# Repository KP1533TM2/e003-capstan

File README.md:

# e003-capstan
Проект блока управления ведущими двигателями ДМ-1, ДМ-5 (применяемые в магнитофонах Олимп, Электроника ТА1-003) с кварцевой стабилизацией.

Основан на коде [контроллера ведущего двигателя самодельной кассетной деки TK-140 leoniv](http://leoniv.diod.club/projects/audio/tk-140/tk-140.html).

ZCD для сетевого напряжения взят и адаптирован [отсюда](https://cdn.hackaday.io/files/1597066832861504/SimpleIsolatedZeroCrossDetector.pdf).

# Отличия от БУВД Олимп 005
- Иной форм-фактор платы (расчитано на доработанный Олимп 003);
- Силовой каскад реализован простым преобразователем напряжения в ток;
- ФАПЧ, формирование синусоидального тока выполнены на микроконтроллере;
- Реализовано торможение при смене скорости кратковременным реверсом;

# Схема
Актуальная версия схемы (для rev1) лежит [тут](/hw/rev1/main.pdf).

# TODO:
- [x] "чистовая" плата - предположительно rev1;
- [ ] АПЧ сетевого напряжения;
- [ ] переключение реле синхронно переходу через 0 для сбережения контактов (?);
- [ ] описание.

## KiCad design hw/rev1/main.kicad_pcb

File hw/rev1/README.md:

# Краткое описание rev1

Ревизия 1 - первая "чистовая" печатная плата.

[Схема этой платы](./main.pdf).

Основные моменты:
* Сложная оригинальная схема петлевого фильтра, модулятора тока и силового
каскада полностью заменена на фильтр ШИМ с преобразователем V→I с применением
полевого транзистора.
* Модуляция синусом реализована таблично и воздействует на выход PID-регулятора.
* Интервал полупериода сетевого напряжения снимается посредством схемы ZCD с
обмотки трансформатора, питающей ведущий двигатель.
* Номиналы схемы ZCD эмпирически подобраны так, чтобы при трехступенчатой форме
сетевого напряжения (с ИБП) схема стабильно формировала лог.0 при "ступеньке"
0В;
* Добавлены крепежные отверстия по периметру.

# Картинки

To be continued...

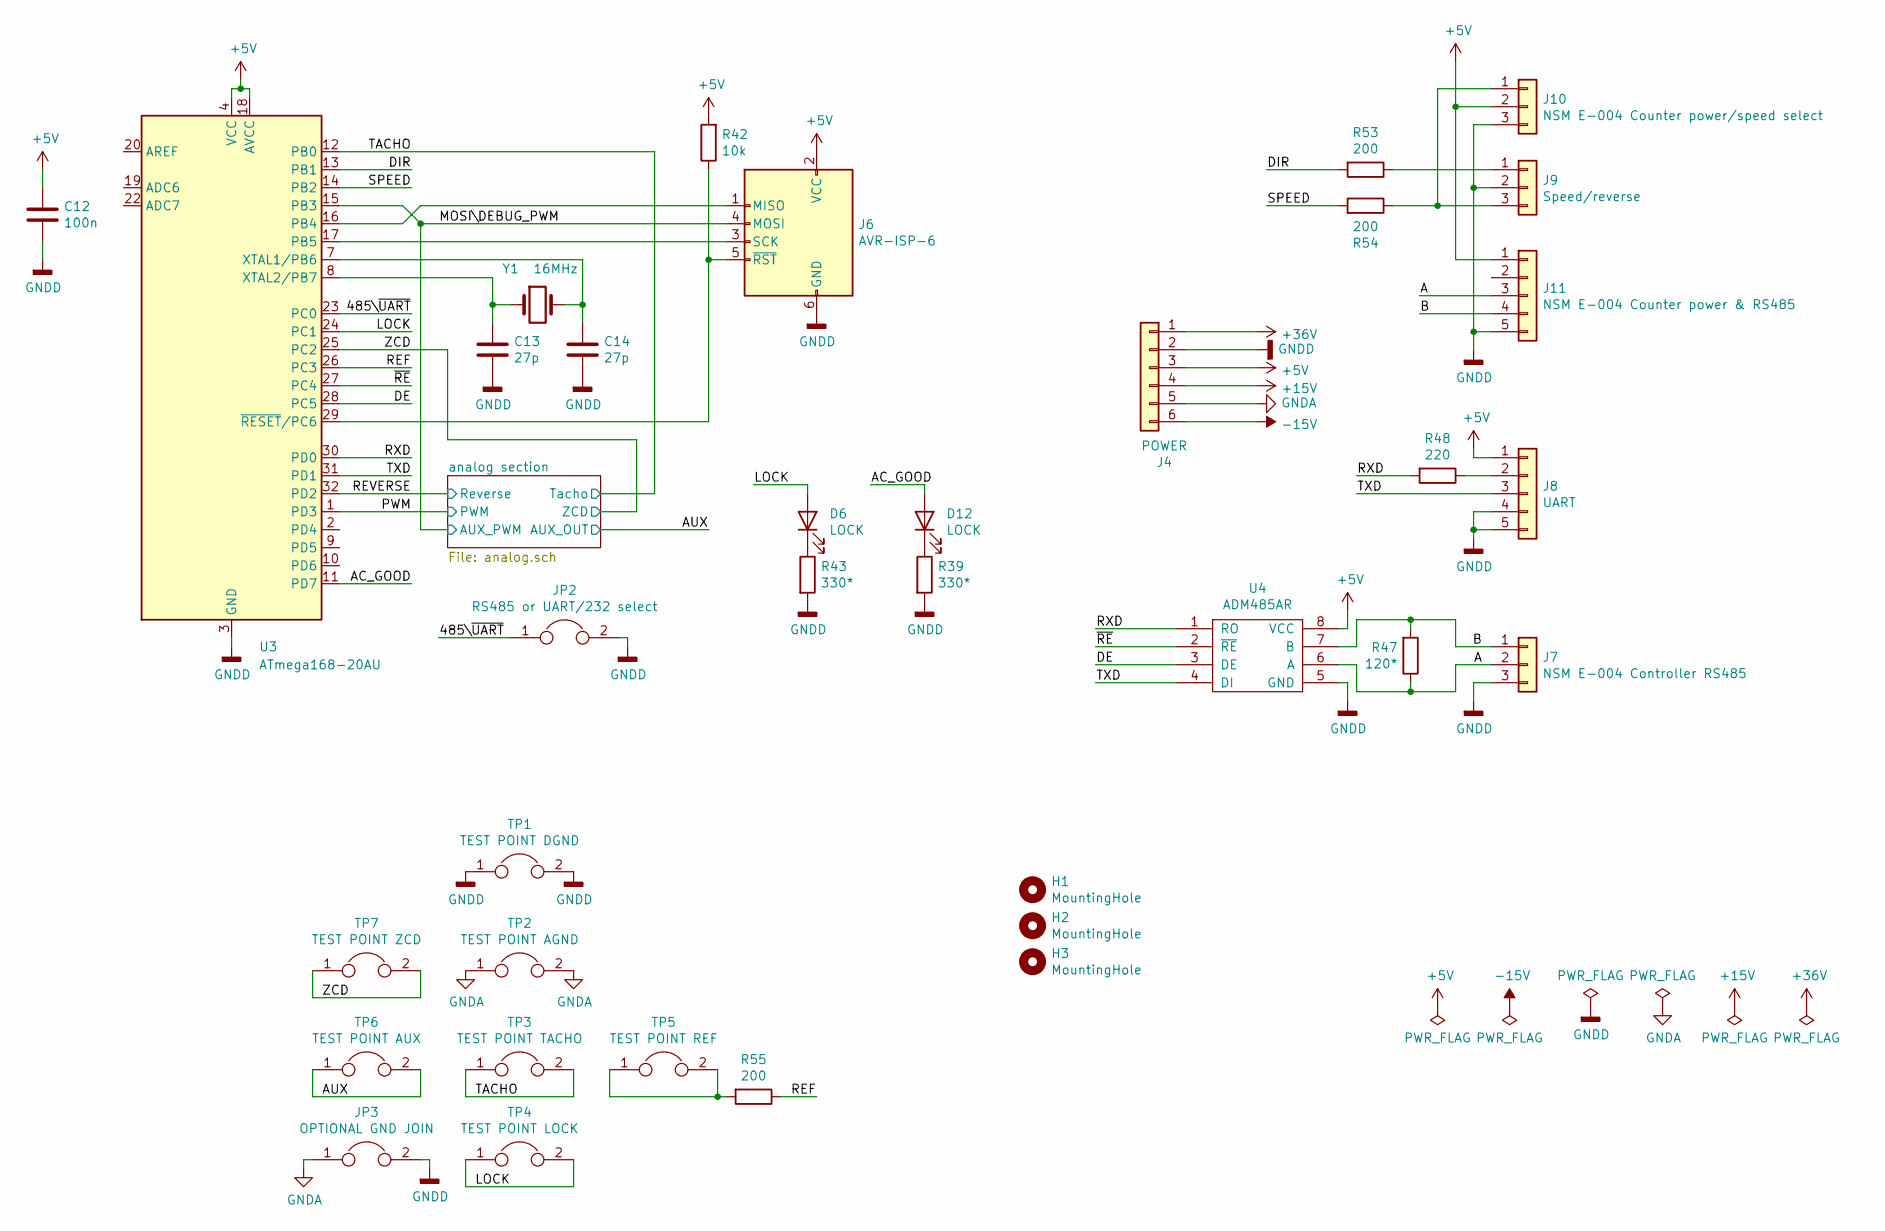
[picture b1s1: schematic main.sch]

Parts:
C12: 100n; C_0805_2012Metric
C13, C14: 27p; C_0805_2012Metric
D6, D12: LOCK; LED_0805_2012Metric
H1, H2, H3: MountingHole; MountingHole_3.2mm_M3
J4: POWER; Molex_KK-396_Right_Angle
J6: AVR-ISP-6; PinHeader_2x03_P2.54mm_Vertical
J7: NSM E-004 Controller RS485; JST_XH_B3B-XH-A_1x03_P2.50mm_Vertical
J8: UART; JST_XH_B5B-XH-A_1x05_P2.50mm_Vertical
J9: Speed/reverse; JST_XH_B3B-XH-A_1x03_P2.50mm_Vertical
J10: NSM E-004 Counter power/speed select; JST_XH_B3B-XH-A_1x03_P2.50mm_Vertical
J11: NSM E-004 Counter power & RS485; JST_XH_B5B-XH-A_1x05_P2.50mm_Vertical
JP2: RS485 or UART/232 select; PinHeader_1x02_P2.54mm_Vertical
JP3: OPTIONAL GND JOIN; SolderJumper-2_P1.3mm_Open_RoundedPad1.0x1.5mm
R39, R43: 330*; R_0805_2012Metric
R42: 10k; R_0805_2012Metric
R47: 120*; R_0805_2012Metric
R48: 220; R_0805_2012Metric
R53, R54, R55: 200; R_0805_2012Metric
TP1: TEST POINT DGND; PinHeader_2x01_P2.54mm_Vertical
TP2: TEST POINT AGND; PinHeader_2x01_P2.54mm_Vertical
TP3: TEST POINT TACHO; PinHeader_2x01_P2.54mm_Vertical
TP4: TEST POINT LOCK; PinHeader_2x01_P2.54mm_Vertical
TP5: TEST POINT REF; PinHeader_2x01_P2.54mm_Vertical
TP6: TEST POINT AUX; PinHeader_2x01_P2.54mm_Vertical
TP7: TEST POINT ZCD; PinHeader_2x01_P2.54mm_Vertical
U3: ATmega168-20AU; TQFP-32_7x7mm_P0.8mm
U4: ADM485AR; SO-8_3.9x4.9mm_P1.27mm
Y1: 16MHz; Crystal_SMD_HC49-SD

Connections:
+5V: C12.1, J4.3, J6.2 (VCC), J8.1, J10.2, J11.1, R42.2, U3.4 (VCC), U3.6 (VCC), U3.18 (AVCC), U4.8 (VCC); also elsewhere on the board
+15V: J4.4; also elsewhere on the board
+36V: J4.1; also elsewhere on the board
-15V: J4.6; also elsewhere on the board
/485\~UART: JP2.1, U3.23 (PC0)
/A: J7.2, J11.3, R47.1, U4.6 (A)
/AC_GOOD: D12.2 (A), U3.11 (PD7)
/AUX: TP6.1, TP6.2; also elsewhere on the board
/B: J7.1, J11.4, R47.2, U4.7 (B)
/DE: U3.28 (PC5), U4.3 (DE)
/DIR: R53.2, U3.13 (PB1)
/LOCK: D6.2 (A), TP4.1, TP4.2, U3.24 (PC1)
/MOSI\DEBUG_PWM: J6.4 (MOSI), U3.15 (PB3); also elsewhere on the board
/PWM: U3.1 (PD3); also elsewhere on the board
/REF: R55.1, U3.26 (PC3)
/REVERSE: U3.32 (PD2); also elsewhere on the board
/RXD: R48.2, U3.30 (PD0), U4.1 (RO)
/SPEED: R54.2, U3.14 (PB2)
/TACHO: TP3.1, TP3.2, U3.12 (PB0); also elsewhere on the board
/TXD: J8.3, U3.31 (PD1), U4.4 (DI)
/ZCD: TP7.1, TP7.2, U3.25 (PC2); also elsewhere on the board
/~RE: U3.27 (PC4), U4.2 (~RE)
GNDA: J4.5, JP3.1, TP2.1, TP2.2; also elsewhere on the board
GNDD: C12.2, C13.2, C14.2, J4.2, J6.6 (GND), J7.3, J8.4, J8.5, J9.2, J10.3, J11.5, JP2.2, JP3.2, R39.2, R43.2, TP1.1, TP1.2, U3.3 (GND), U3.5 (GND), U3.21 (GND), U4.5 (GND); also elsewhere on the board
unnamed: C13.1, U3.8 (XTAL2/PB7), Y1.1
unnamed: C14.1, U3.7 (XTAL1/PB6), Y1.2
unnamed: D6.1 (K), R43.1
unnamed: D12.1 (K), R39.1
unnamed: J6.1 (MISO), U3.16 (PB4)
unnamed: J6.3 (SCK), U3.17 (PB5)
unnamed: J6.5 (~RST), R42.1, U3.29 (~RESET~/PC6)
unnamed: J8.2, R48.1
unnamed: J9.1, R53.1
unnamed: J9.3, J10.1, R54.1
unnamed: R55.2, TP5.1, TP5.2

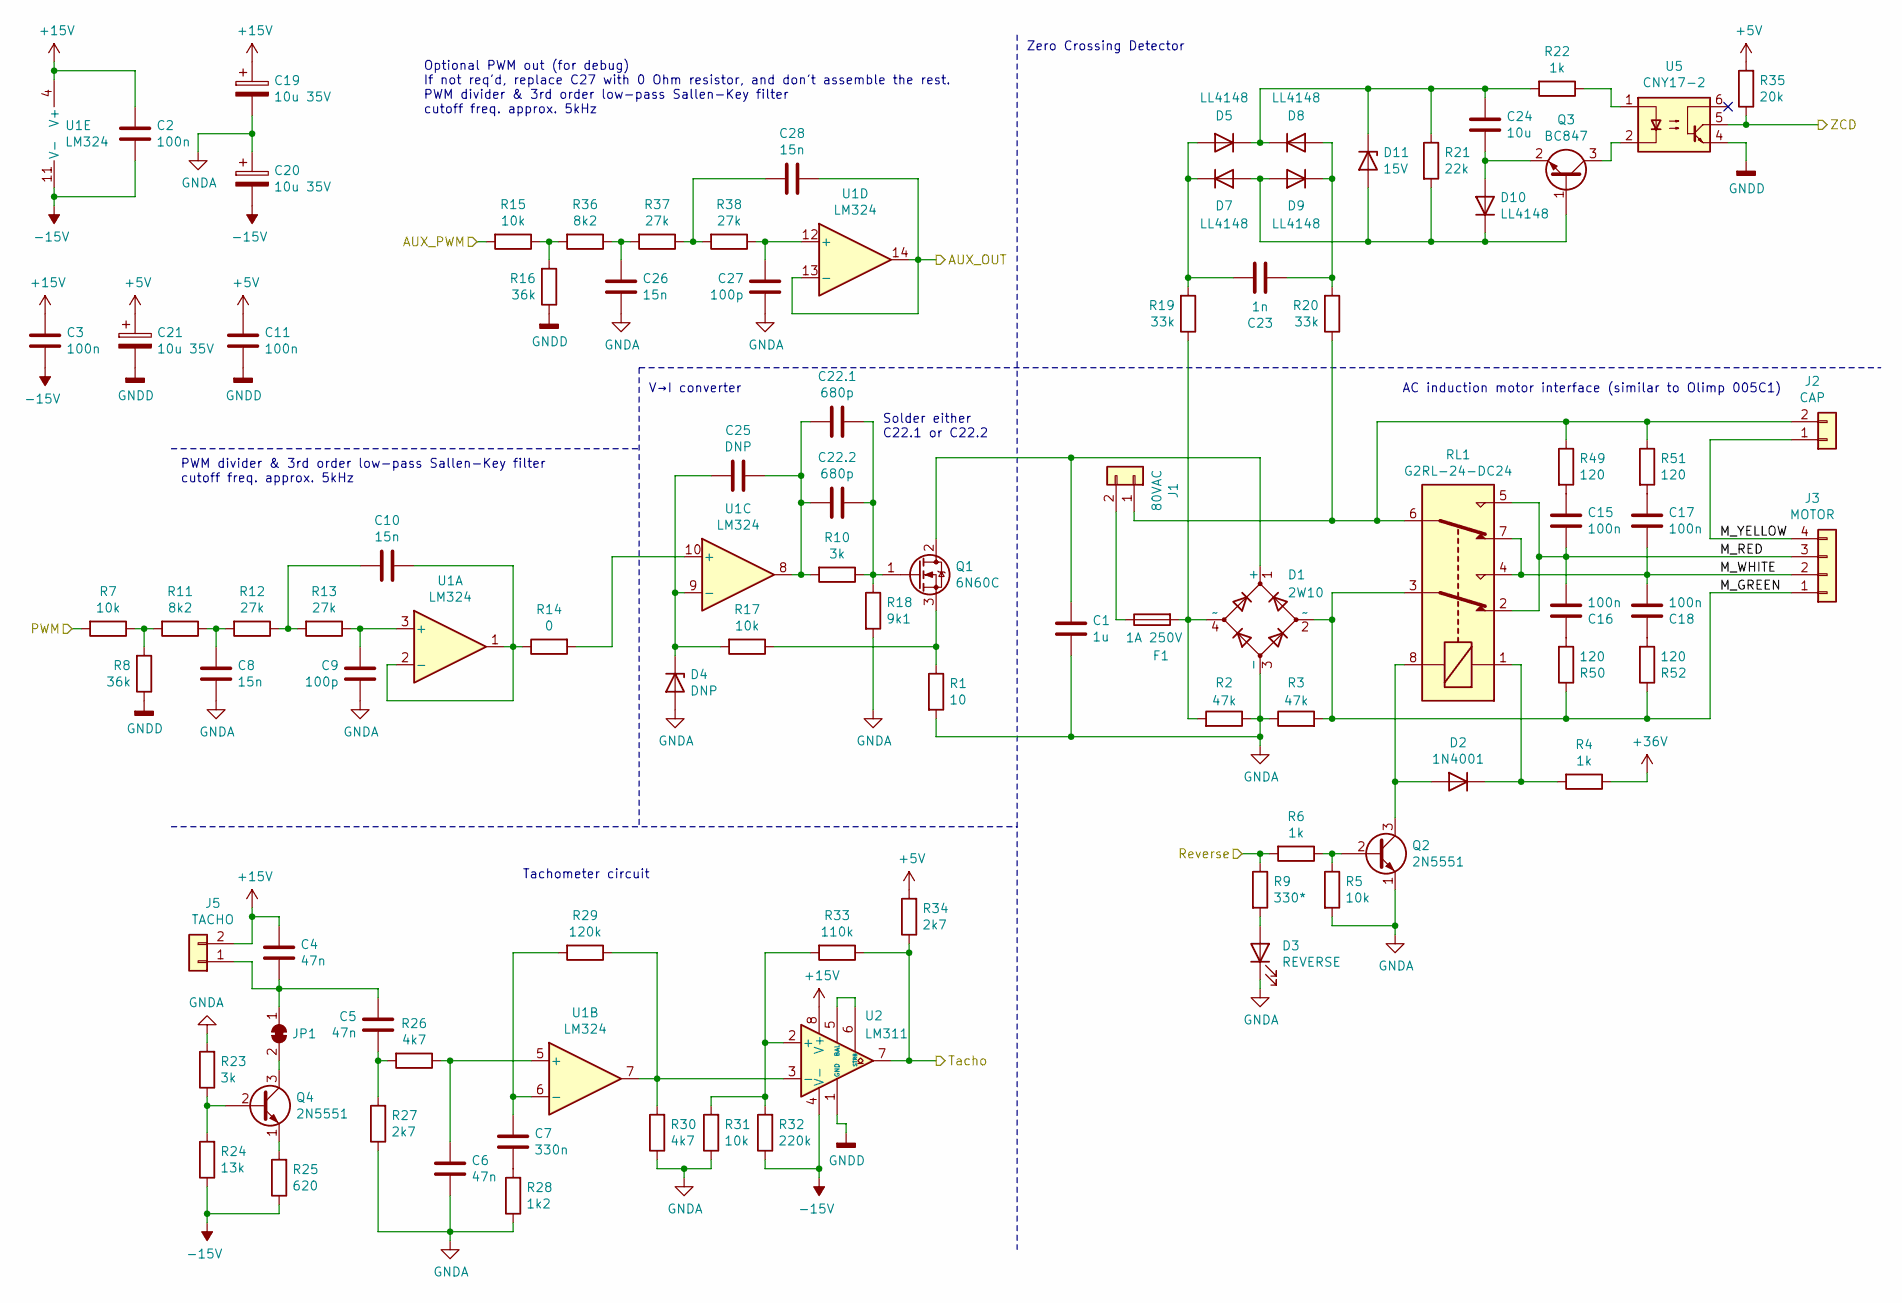
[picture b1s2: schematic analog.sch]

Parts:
C1: 1u; C_Rect_L29.0mm_W12.2mm_P27.50mm_MKT
C2, C3, C11: 100n; C_0805_2012Metric
C4, C5, C6: 47n; C_0805_2012Metric
C7: 330n; C_0805_2012Metric
C8, C10, C26, C28: 15n; C_0805_2012Metric
C9, C27: 100p; C_0805_2012Metric
C15, C16, C17, C18: 100n; C_Rect_L13.0mm_W4.0mm_P10.00mm_FKS3_FKP3_MKS4
C19, C20, C21: 10u 35V; CP_EIA-6032-28_Kemet-C
C22.1: 680p; C_Rect_L7.0mm_W4.5mm_P5.00mm
C22.2: 680p; C_0805_2012Metric
C23: 1n; C_1206_3216Metric
C24: 10u; C_1206_3216Metric
C25: DNP; C_0805_2012Metric
D1: 2W10; Diode_Bridge_Round_D9.8mm
D2: 1N4001; D_DO-41_SOD81_P5.08mm_Vertical_KathodeUp
D3: REVERSE; LED_0805_2012Metric
D4: DNP; D_SOD-123
D5, D7, D8, D9, D10: LL4148; D_MiniMELF
D11: 15V; D_SOD-123
F1: 1A 250V; Fuse_Littelfuse_372_D8.50mm
J1: 80VAC; TerminalBlock_bornier-2_P5.08mm
J2: CAP; TerminalBlock_bornier-2_P5.08mm
J3: MOTOR; TerminalBlock_bornier-4_P5.08mm
J5: TACHO; Molex_KK-254_AE-6410-02A_1x02_P2.54mm_Vertical
JP1: SolderJumper_2_Bridged; SolderJumper-2_P1.3mm_Bridged_RoundedPad1.0x1.5mm
Q1: 6N60C; TO-220F-3_Horizontal_TabDown_no_silk
Q2, Q4: 2N5551; TO-92L_Inline_Wide
Q3: BC847; SOT-23
R1: 10; R_Axial_DIN0922_L20.0mm_D9.0mm_P30.48mm_Horizontal
R2, R3: 47k; R_Axial_DIN0207_L6.3mm_D2.5mm_P5.08mm_Vertical
R4: 1k; R_Axial_DIN0614_L14.3mm_D5.7mm_P5.08mm_Vertical
R5, R7, R15, R31: 10k; R_0805_2012Metric
R6: 1k; R_0805_2012Metric
R8, R16: 36k; R_0805_2012Metric
R9: 330*; R_0805_2012Metric
R10: 3k; R_Axial_DIN0207_L6.3mm_D2.5mm_P10.16mm_Horizontal
R11, R36: 8k2; R_0805_2012Metric
R12, R13, R37, R38: 27k; R_0805_2012Metric
R14: 0; R_0805_2012Metric
R17: 10k; R_Axial_DIN0207_L6.3mm_D2.5mm_P10.16mm_Horizontal
R18: 9k1; R_Axial_DIN0207_L6.3mm_D2.5mm_P10.16mm_Horizontal
R19, R20: 33k; R_1206_3216Metric
R21: 22k; R_1206_3216Metric
R22: 1k; R_1206_3216Metric
R23: 3k; R_0805_2012Metric
R24: 13k; R_0805_2012Metric
R25: 620; R_0805_2012Metric
R26, R30: 4k7; R_0805_2012Metric
R27, R34: 2k7; R_0805_2012Metric
R28: 1k2; R_0805_2012Metric
R29: 120k; R_0805_2012Metric
R32: 220k; R_0805_2012Metric
R33: 110k; R_0805_2012Metric
R35: 20k; R_0805_2012Metric
R49, R50, R51, R52: 120; R_Axial_DIN0309_L9.0mm_D3.2mm_P5.08mm_Vertical
RL1: G2RL-24-DC24; Relay_DPDT_Omron_G2RL
U1: LM324; SO-14_3.9x8.65mm_P1.27mm
U2: LM311; SO-8_3.9x4.9mm_P1.27mm
U5: CNY17-2; DIP-6_W7.62mm_LongPads

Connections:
+5V: C11.1, C21.1, R34.2, R35.2; also elsewhere on the board
+15V: C2.1, C3.1, C4.1, C19.1, J5.2, U1.4 (V+), U2.8 (V+); also elsewhere on the board
+36V: R4.1; also elsewhere on the board
-15V: C2.2, C3.2, C20.2, R24.1, R25.1, R32.1, U1.11 (V-), U2.4 (V-); also elsewhere on the board
/AUX: C28.1, U1.13 (-), U1.14; also elsewhere on the board
/MOSI\DEBUG_PWM: R15.2; also elsewhere on the board
/PWM: R7.2; also elsewhere on the board
/REVERSE: R6.2, R9.1; also elsewhere on the board
/TACHO: R33.1, R34.1, U2.7; also elsewhere on the board
/ZCD: R35.1, U5.5; also elsewhere on the board
/analog section/M_GREEN: D1.2 (~~), J3.1, R3.2, R50.1, R52.1, RL1.3
/analog section/M_RED: C15.2, C16.2, J3.3, RL1.2, RL1.5
/analog section/M_WHITE: C17.2, C18.2, J3.2, RL1.4, RL1.7
/analog section/M_YELLOW: J2.1, J3.4
GNDA: C1.2, C6.2, C8.2, C9.2, C19.2, C20.1, C26.2, C27.2, D1.3 (-), D3.1 (K), D4.2 (A), Q2.1 (E), R1.2, R2.1, R3.1, R5.2, R18.2, R23.2, R27.1, R28.1, R30.1, R31.1; also elsewhere on the board
GNDD: C11.2, C21.2, R8.1, R16.1, U2.1 (GND), U5.4; also elsewhere on the board
unnamed: C1.1, D1.1 (+), Q1.2 (D)
unnamed: C4.2, C5.1, J5.1, JP1.1 (A)
unnamed: C5.2, R26.2, R27.2
unnamed: C6.1, R26.1, U1.5 (+)
unnamed: C7.1, R29.2, U1.6 (-)
unnamed: C7.2, R28.2
unnamed: C8.1, R11.1, R12.2
unnamed: C9.1, R13.1, U1.3 (+)
unnamed: C10.1, R14.1, U1.1, U1.2 (-)
unnamed: C10.2, R12.1, R13.2
unnamed: C15.1, R49.2
unnamed: C16.1, R50.2
unnamed: C17.1, R51.2
unnamed: C18.1, R52.2
unnamed: C22.1.1, C22.2.1, Q1.1 (G), R10.1, R18.1
unnamed: C22.1.2, C22.2.2, C25.1, R10.2, U1.8
unnamed: C23.1, D5.2 (A), D7.1 (K), R19.2
unnamed: C23.2, D8.2 (A), D9.1 (K), R20.2
unnamed: C24.1, D5.1 (K), D8.1 (K), D11.1 (K), R21.1, R22.2
unnamed: C24.2, D10.2 (A), Q3.2 (E)
unnamed: C25.2, D4.1 (K), R17.2, U1.9 (-)
unnamed: C26.1, R36.1, R37.2
unnamed: C27.1, R38.1, U1.12 (+)
unnamed: C28.2, R37.1, R38.2
unnamed: D1.4 (~~), F1.2, R2.2, R19.1
unnamed: D2.1 (K), R4.2, RL1.1
unnamed: D2.2 (A), Q2.3 (C), RL1.8
unnamed: D3.2 (A), R9.2
unnamed: D7.2 (A), D9.2 (A), D10.1 (K), D11.2 (A), Q3.1 (B), R21.2
unnamed: F1.1, J1.2
unnamed: J1.1, J2.2, R20.1, R49.1, R51.1, RL1.6
unnamed: JP1.2 (B), Q4.3 (C)
unnamed: Q1.3 (S), R1.1, R17.1
unnamed: Q2.2 (B), R5.1, R6.1
unnamed: Q3.3 (C), U5.2
unnamed: Q4.1 (E), R25.2
unnamed: Q4.2 (B), R23.1, R24.2
unnamed: R7.1, R8.2, R11.2
unnamed: R14.2, U1.10 (+)
unnamed: R15.1, R16.2, R36.2
unnamed: R22.1, U5.1
unnamed: R29.1, R30.2, U1.7, U2.3 (-)
unnamed: R31.2, R32.2, R33.2, U2.2 (+)
unnamed: U2.5 (BAL), U2.6 (STRB)

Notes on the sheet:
PWM divider & 3rd order low-pass Sallen-Key filter cutoff freq. approx. 5kHz
V→I converter
Tachometer circuit
AC induction motor interface (similar to Olimp 005C1)
Zero Crossing Detector
Optional PWM out (for debug) If not req'd, replace C27 with 0 Ohm resistor, and don't assemble the rest. PWM divider & 3rd order low-pass Sallen-Key filter cutoff freq. approx. 5kHz
Solder either C22.1 or C22.2

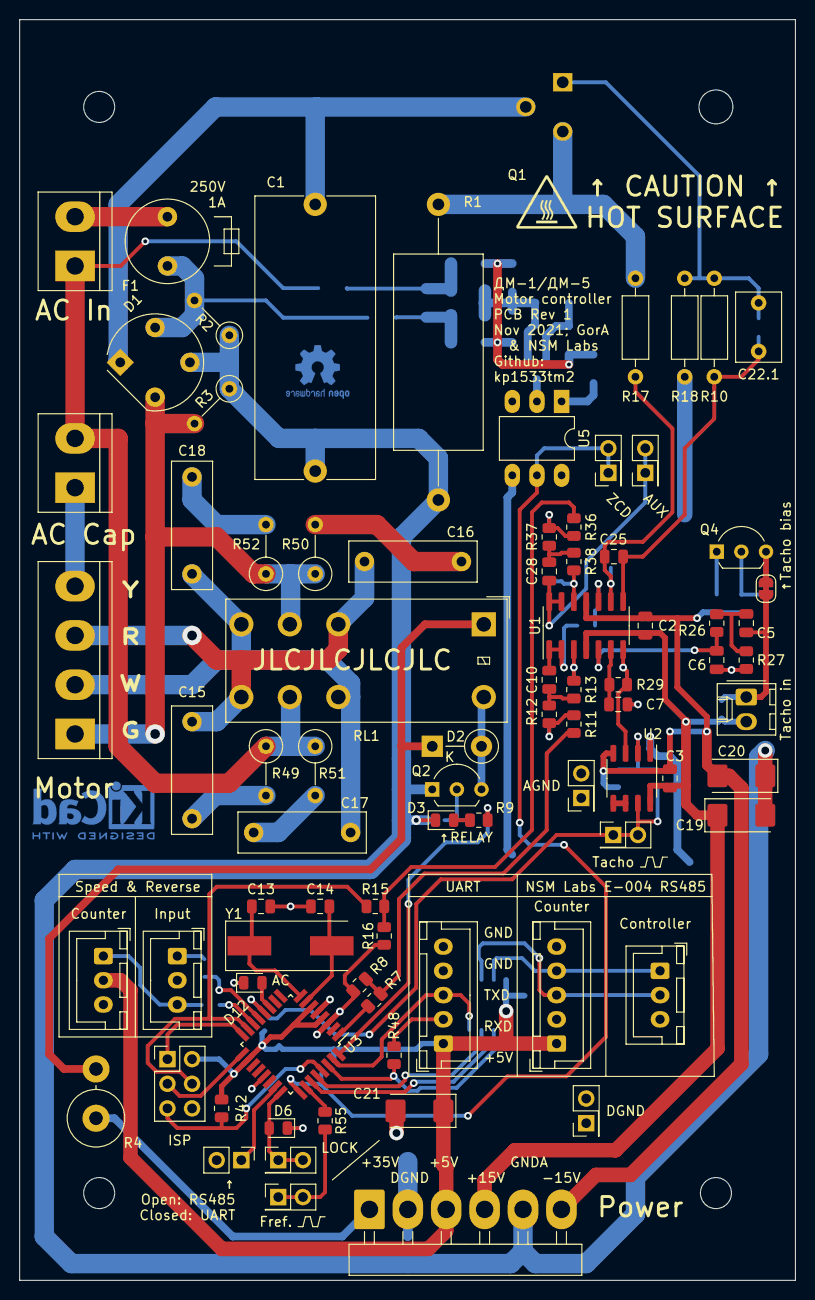
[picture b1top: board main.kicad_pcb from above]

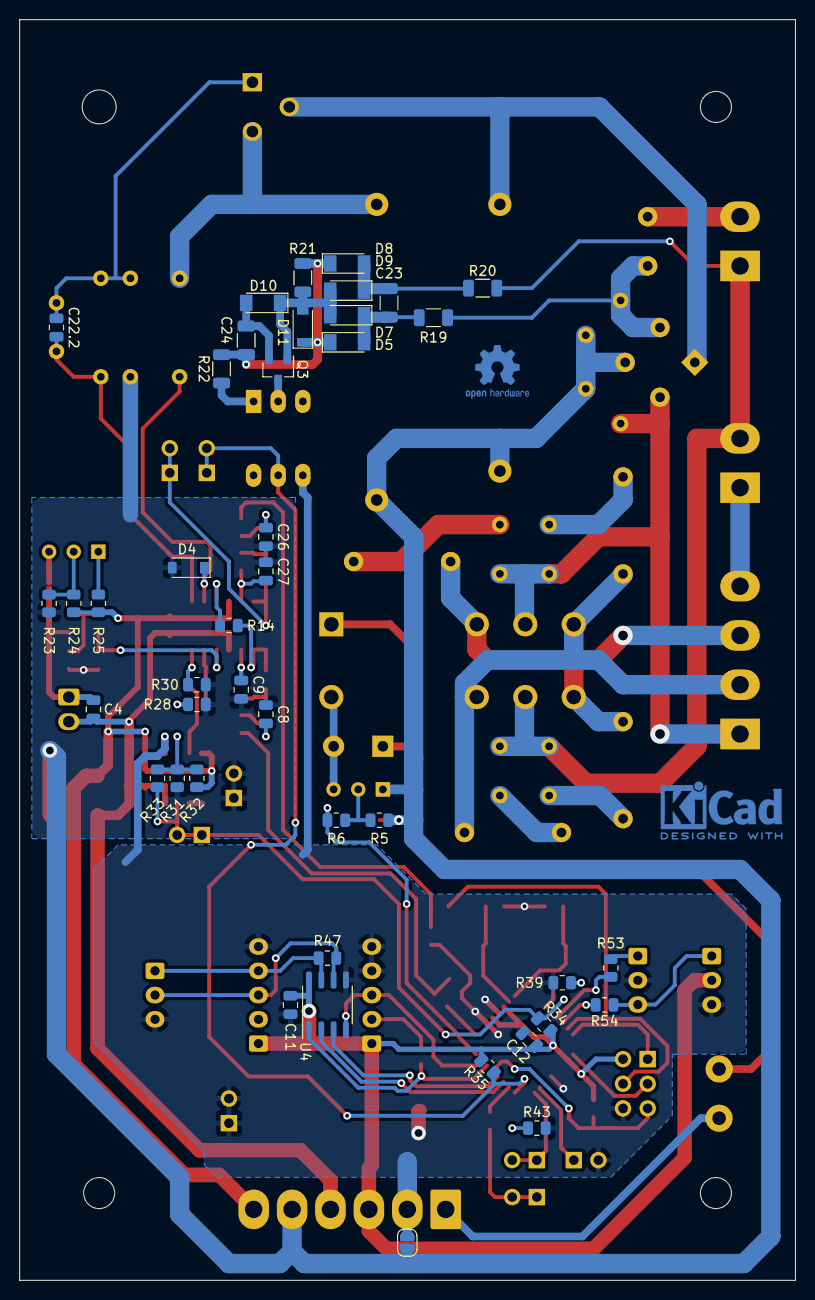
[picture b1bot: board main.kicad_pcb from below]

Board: 2 copper layers, 80.0 x 130.0 mm, 127 parts (42 on the bottom side), 83 nets.

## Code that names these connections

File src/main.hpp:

//----------------------------------------------------------------------------

//Главный модуль, заголовочный файл

//----------------------------------------------------------------------------

#ifndef MAIN_HPP
#define MAIN_HPP

//----------------------------------------------------------------------------

#include <ioavr.h>
#include <intrinsics.h>
#define __STDC_LIMIT_MACROS
#include <stdint.h>
#include <stdbool.h>
#include "gpio.hpp"
#include "systimer.hpp"

//-------------------------- Номер версии firmware: --------------------------

#define VERSION "1.00"

//-------------- Использование выводов процессора [module]: ------------------

typedef TGpio<PORT_C, PIN_1> Pin_Led_t;   //PC1 - LED out [control]
typedef TGpio<PORT_D, PIN_2> Pin_Relay_t; //PD2 - Reverse relay
typedef TGpio<PORT_C, PIN_3> Pin_Fref_t;  //PC3 - Fref out (oscilloscope) (normally PC3)
typedef TGpio<PORT_C, PIN_4> Pin_Debug_t; //PC4 - Oscilloscope debug out
typedef TGpio<PORT_B, PIN_1> Pin_Dir_t;   //PB1 - Reverse [control]
typedef TGpio<PORT_B, PIN_2> Pin_Spd1_t;  //PB2 - Speed 1 [control], 9/19

typedef TGpio<PORT_B, PIN_0> Pin_Tacho_t; //PB0 (ICP0) - Tacho in [control]
typedef TGpio<PORT_D, PIN_3> Pin_Pwm_t;   //PB3 (OC2B) - PWM out [pwm]
typedef TGpio<PORT_C, PIN_2> Pin_Zcd_t;   //PC2 - Zero Crossing Detector

typedef TGpio<PORT_D, PIN_0> Pin_RXD_t;   //PD0 (RXD) - RXD [wakeport]
typedef TGpio<PORT_D, PIN_1> Pin_TXD_t;   //PD1 (TXD) - TXD [wakeport]

typedef TGpio<PORT_D, PIN_4> Pin_Lock_t;  //PD4 - Lock out [control] NOT USED
typedef TGpio<PORT_D, PIN_5> Pin_Sleep_t; //PD5 - Sleep [control] NOT USED
//typedef TGpio<PORT_D, PIN_6> Pin_Spd2_t;  //PD6 - Speed 2 [control], FWD/REV

//-------------- Использование аппаратных блоков процессора: -----------------

//Timer0: system timer [systimer]
//Timer1: reference divider [pll]
//Timer2: PWM generation [pwm]
//USART: computer port [wakeport]
//Comparator : NOT USED
//ADC: NOT USED
//SPI: NOT USED
//TWI: NOT USED

//----------------------- Использование прерываний: --------------------------

//TIMER0_COMPA: system tick [systimer]
//TIMER1_CAPT: speed sensor [pll]
//TIMER1_COMPA: phase estimation [pll]
//TIMER2_COMPA: delta-sigma modulator [pwm]

//---------------------------- Макроопределения: -----------------------------

#define LO(x)    ((uint8_t)((x) & 0xFF))
#define HI(x)    ((uint8_t)(((x) >> 8) & 0xFF))
#define BYTE1(x) (LO(x))
#define BYTE2(x) (HI(x))
#define BYTE3(x) ((uint8_t)(((uint32_t)(x) >> 16) & 0xFF))
#define BYTE4(x) ((uint8_t)(((uint32_t)(x) >> 24) & 0xFF))

#define WORD(b1,b0)        (((uint16_t)(b1) << 8) | (b0))
#define DWORD(b3,b2,b1,b0) (((uint32_t)WORD(b3,b2) << 16) | WORD(b1,b0))

#define ABS(x) ((x < 0)? -x : x)

#ifndef NULL
  #define NULL _NULL
#endif

//----------------------------------------------------------------------------

#endif

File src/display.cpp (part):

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//к выходам внешнего сдвигового регистра (цепочка из 6-ти 74HC595).
//Загрузка регистра осуществляется с помощью аппаратного порта SPI.
//Для доступа к регистру реализован класс TSreg.
//Задействованы порты: SCLK - PB5 (SPI SCK), SDATA - PB3 (SPI MOSI),
//LOAD - PC0, OE - PC1.

//Реализован вывод времени в формате "-9.59.59", метража в формате
//"-9999.9", скорости в формате "999.999" и диаметра ролика в формате
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
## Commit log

2021-03-27 Добавлен проект контроллера ведущего двигателя магнитофона ТК-140 авторства leoniv
2021-03-28 Добавлен .gitignore
2021-03-28 Переработка для Arduino Mega 2560 и двигатель ДМ-5
    * Timer1 -> Timer4, PL0 (ICP4) - пин 49 - вход таходатчика
    * Timer2 PWM не изменился - пин 10 - ШИМ управления мотором
    Схема таходатчика как у leoniv, управляющее напряжение формируется
    через пассивный ФНЧ 220н/10кОм.
2021-03-29 Светодиод Arduino теперь показывает захват
2021-03-31 Добавлен проект программы-пульта
2021-06-14 Регуляция PID работает по скользящему усреднению 8 отсчетов фазы.
2021-06-16 Переработка с ардуины на первую печатную плату. Изменены PID по умолчанию.
2021-06-16 Добавлено торможение реле при смене скорости.
2021-06-19 Добавлены исходники макетной печатной платы и схемы
2021-06-21 Добавлено README
2021-06-21 Добавлена незаконченная чистовая схема rev1, симуляция фильтра ШИМ для ngspice.
2021-06-21 Обновлен README
2021-06-21 Добавлены фото прототипа rev0
2021-06-21 README дополнен фото
2021-06-21 В схему добавлен забытый ZCD.
2021-11-02 Добавлена печатная плата rev1 (вероятно чистовая).
    + Обозначена и разведена схема ZCD;
    + Исключена схема аналогового перемножителя;
    * модуляция модулем синуса полностью цифровая;
    + LM324 использована полностью:
    * собран 2й PWM фильтр, подключенный к OC2A в отладочных целях;
    + Добавлен доп. светодиод, предназначенный для контроля за ZCD;
2021-11-02 Опечатка + немного описания ревизий.
2021-11-02 Опечатка.
2021-11-02 Документация.
